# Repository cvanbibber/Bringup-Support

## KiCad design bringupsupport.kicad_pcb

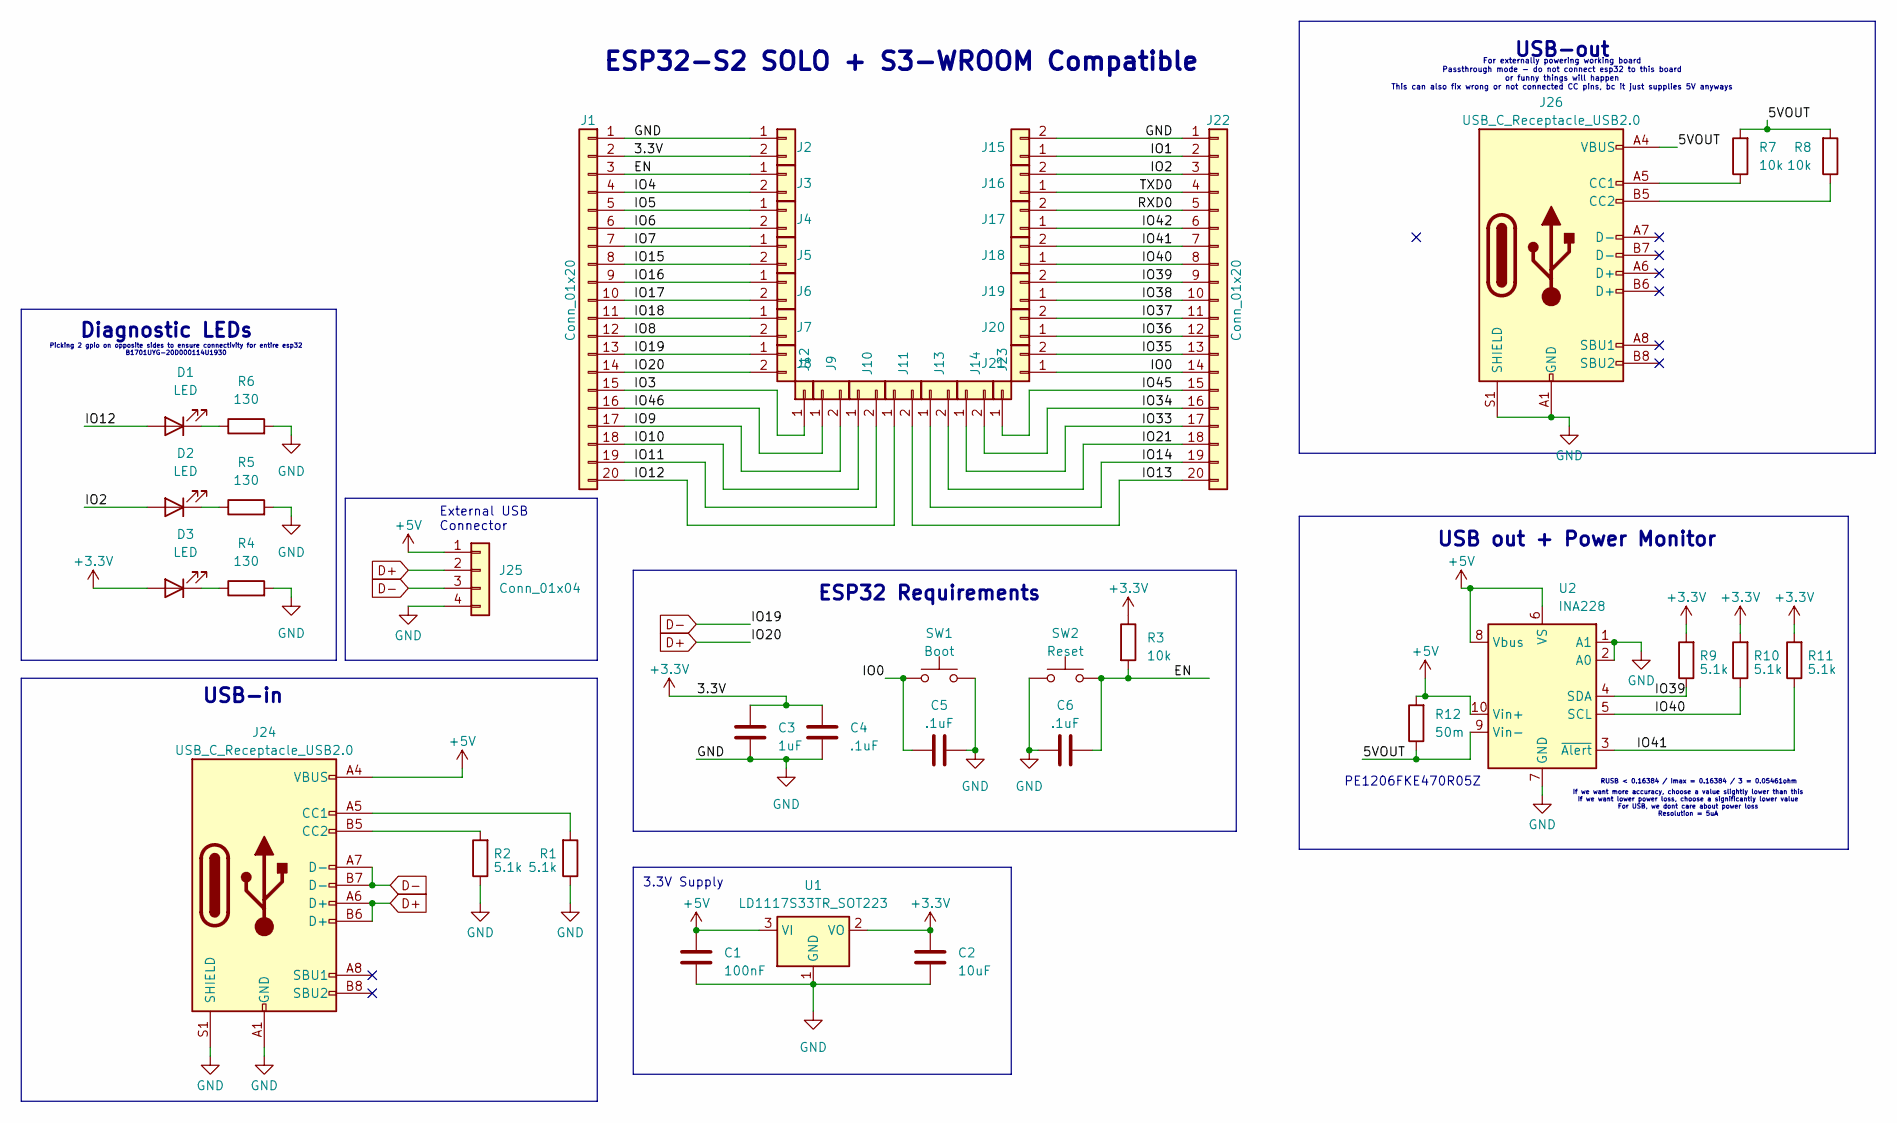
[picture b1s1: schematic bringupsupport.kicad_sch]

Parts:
C1: 100nF; C_0805_2012Metric_Pad1.18x1.45mm_HandSolder
C2: 10uF; C_0805_2012Metric_Pad1.18x1.45mm_HandSolder
C3: 1uF; C_0805_2012Metric_Pad1.18x1.45mm_HandSolder
C4, C5, C6: .1uF; C_0805_2012Metric_Pad1.18x1.45mm_HandSolder
D1, D2, D3: LED; D_0805_2012Metric_Pad1.15x1.40mm_HandSolder
J1, J22: Conn_01x20; PinHeader_1x20_P2.54mm_Vertical
J2, J3, J4, J5, J6, J7, J8, J9, J10, J11, J13, J14, J15, J16, J17, J18, J19, J20, J21: Conn_01x02; FlexyPin_1x02_P1.27mm
J12, J23: Conn_01x01; FlexyPin_1x01_P1.27mm
J24, J26: USB_C_Receptacle_USB2.0; USB_C_Receptacle_GCT_USB4105-xx-A_16P_TopMnt_Horizontal
J25: Conn_01x04; PinHeader_1x04_P2.54mm_Vertical
R1, R2, R9, R10, R11: 5.1k; R_0805_2012Metric_Pad1.20x1.40mm_HandSolder
R3, R7, R8: 10k; R_0805_2012Metric_Pad1.20x1.40mm_HandSolder
R4, R5, R6: 130; R_0805_2012Metric_Pad1.20x1.40mm_HandSolder
R12: 50m; R_1206_3216Metric_Pad1.30x1.75mm_HandSolder
SW1: Boot; SW_PUSH-12mm
SW2: Reset; SW_PUSH-12mm
U1: LD1117S33TR_SOT223; SOT-223-3_TabPin2
U2: INA228; VSSOP-10_3x3mm_P0.5mm

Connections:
+3.3V: C2.1, C3.1, C4.1, D3.2 (A), J1.2, J2.2, R3.1, R9.2, R10.2, R11.2, U1.2 (VO)
+5V: C1.1, J24.A4 (VBUS), J24.A9 (VBUS), J24.B4 (VBUS), J24.B9 (VBUS), J25.1, R12.2, U1.3 (VI), U2.6 (VS), U2.8 (Vbus), U2.10 (Vin+)
/5VOUT: J26.A4 (VBUS), J26.A9 (VBUS), J26.B4 (VBUS), J26.B9 (VBUS), R7.2, R8.2, R12.1, U2.9 (Vin-)
/EN: C6.2, J1.3, J3.1, R3.2, SW2.2
/IO0: C5.1, J21.1, J22.14, SW1.1
/IO1: J15.1, J22.2
/IO2: D2.2 (A), J16.2, J22.3
/IO3: J1.15, J12.1
/IO4: J1.4, J3.2
/IO5: J1.5, J4.1
/IO6: J1.6, J4.2
/IO7: J1.7, J5.1
/IO8: J1.12, J7.2
/IO9: J1.17, J9.2
/IO10: J1.18, J10.1
/IO11: J1.19, J10.2
/IO12: D1.2 (A), J1.20, J11.1
/IO13: J11.2, J22.20
/IO14: J13.1, J22.19
/IO15: J1.8, J5.2
/IO16: J1.9, J6.1
/IO17: J1.10, J6.2
/IO18: J1.11, J7.1
/IO21: J13.2, J22.18
/IO33: J14.1, J22.17
/IO34: J14.2, J22.16
/IO35: J21.2, J22.13
/IO36: J20.1, J22.12
/IO37: J20.2, J22.11
/IO38: J19.1, J22.10
/IO39: J19.2, J22.9, R9.1, U2.4 (SDA)
/IO40: J18.1, J22.8, R10.1, U2.5 (SCL)
/IO41: J18.2, J22.7, R11.1, U2.3 (~Alert)
/IO42: J17.1, J22.6
/IO45: J22.15, J23.1
/IO46: J1.16, J9.1
/RXD0: J17.2, J22.5
/TXD0: J16.1, J22.4
D+: J1.14, J8.2, J24.A6 (D+), J24.B6 (D+), J25.2
D-: J1.13, J8.1, J24.A7 (D-), J24.B7 (D-), J25.3
GND: C1.2, C2.2, C3.2, C4.2, C5.2, C6.1, J1.1, J2.1, J15.2, J22.1, J24.A1 (GND), J24.A12 (GND), J24.B1 (GND), J24.B12 (GND), J24.S1 (SHIELD), J25.4, J26.A1 (GND), J26.A12 (GND), J26.B1 (GND), J26.B12 (GND), J26.S1 (SHIELD), R1.1, R2.1, R4.2, R5.2, R6.2, SW1.2, SW2.1, U1.1 (GND), U2.1 (A1), U2.2 (A0), U2.7 (GND)
unnamed: D1.1 (K), R6.1
unnamed: D2.1 (K), R5.1
unnamed: D3.1 (K), R4.1
unnamed: J24.A5 (CC1), R1.2
unnamed: J24.B5 (CC2), R2.2
unnamed: J26.A5 (CC1), R7.1
unnamed: J26.B5 (CC2), R8.1

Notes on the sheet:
Picking 2 gpio on opposite sides to ensure connectivity for entire esp32 B1701UYG-20D000114U1930
3.3V Supply
Diagnostic LEDs
PE1206FKE470R05Z
For externally powering working board Passthrough mode - do not connect esp32 to this board or funny things will happen This can also fix wrong or not connected CC pins, bc it just supplies 5V anyways
If we want more accuracy, choose a value slightly lower than this If we want lower power loss, choose a significantly lower value For USB, we dont care about power loss Resolution = 5uA
USB-out
ESP32 Requirements
RUSB < 0.16384 / Imax = 0.16384 / 3 = 0.05461ohm
External USB Connector
USB out + Power Monitor
USB-in
ESP32-S2 SOLO + S3-WROOM Compatible

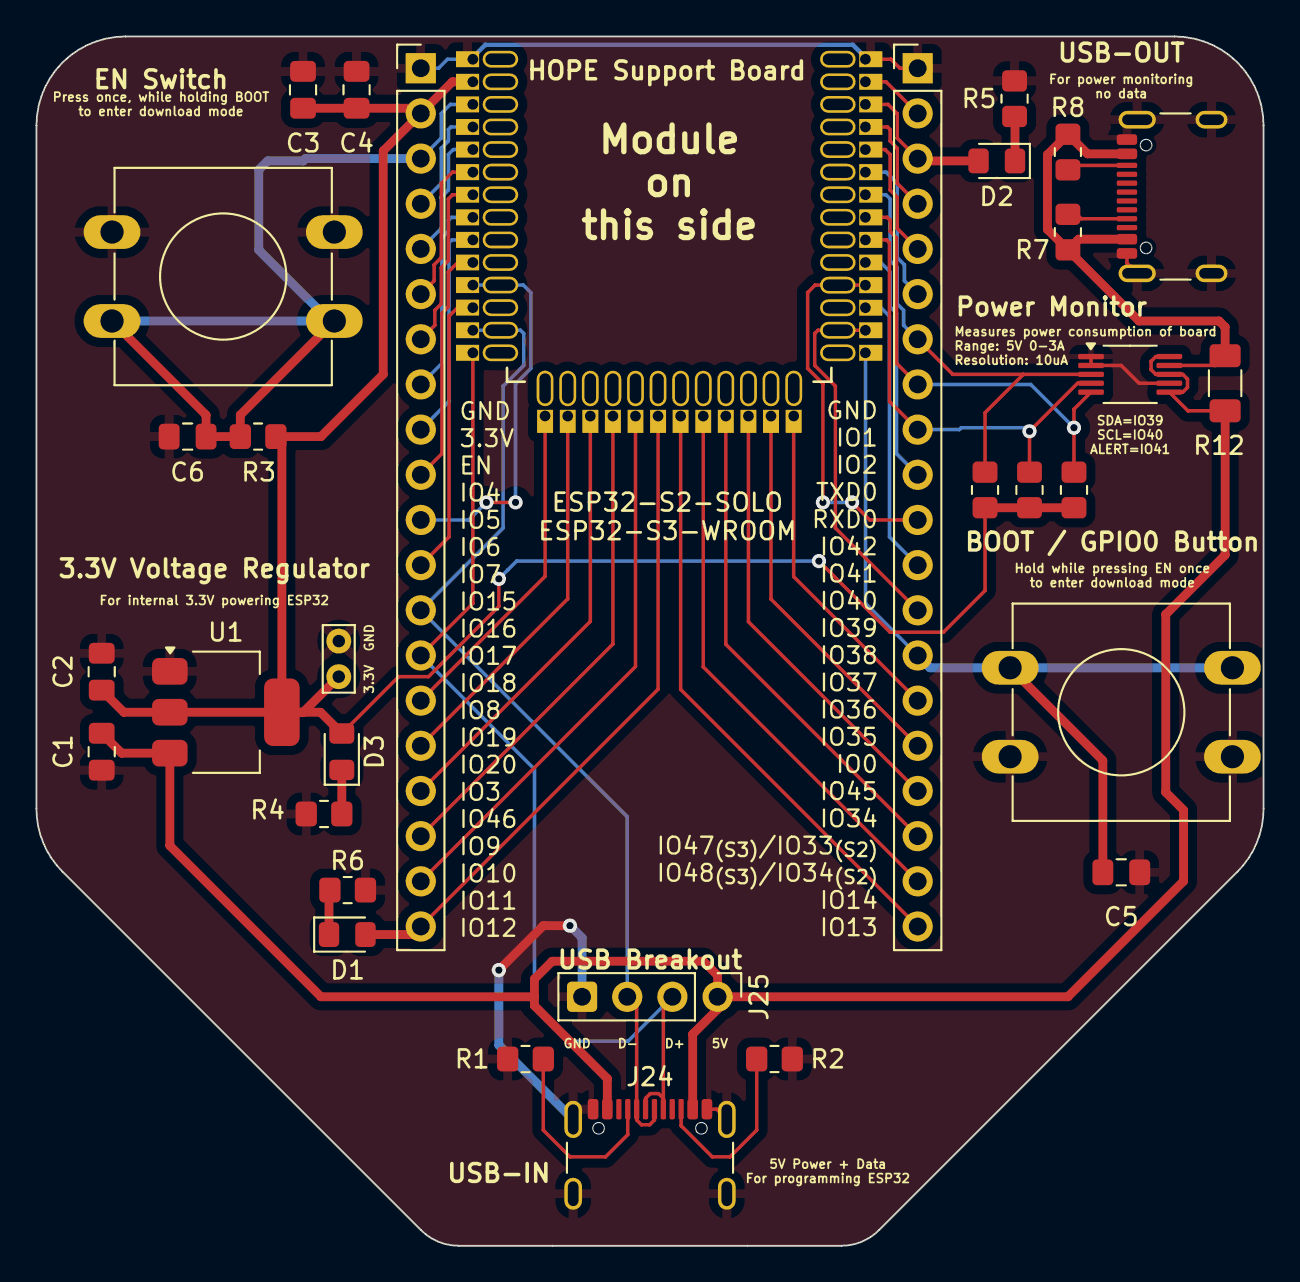
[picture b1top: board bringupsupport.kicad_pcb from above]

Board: 2 copper layers, 69.0 x 68.0 mm, 51 parts (0 on the bottom side), 48 nets.

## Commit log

2025-02-17 bringup support first commit
    working board
